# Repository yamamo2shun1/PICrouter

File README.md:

<div align="center">
<table>
<tr>
<th colspan="4" align="center">INDEX</th>
</tr>
<tr align="center">
    <td><a href="#how-to-buy">How to buy</a></td>
    <td><a href="#licenses">Licenses</a></td>
    <td><a href="#specifications">Specifications</a></td>
    <td><a href="#pin-assign">Pin Assign</a></td>
</tr>
<tr align="center">
    <td><a href="#development">Development</a></td>
    <td><a href="#bootloader-application">Bootloader App.</a></td>
    <td><a href="#schematic-and-board-current-ver-is-100">Sch & Brd Data</a></td>
    <td><a href="#application-projects">App. Projects</a></td>
</tr>
<tr align="center">
    <td><a href="#tutorial-jp">Tutorial (JP)</a></td>
    <td><a href="#tutorial-en">Tutorial (EN)</a></td>
    <td><a href="#supported-osc-messages">Supported OSC Msgs</a></td>
    <td><a href="#supported-hid-commands">Supported HID Cmds</a></td>
</tr>
</table>
</div>

PICrouter
======
PICrouter is a versatile and prototyping board specialized for [Open Sound Control].  
The main function is to communicate between OSC and USB-MIDI/HID.

PICrouter will be an useful with the following purpose.

* Develop an OSC/MIDI/HID controller for music or visual.
* Study a PIC32 microcontroller.
* Study a communication with usb and ethernet.
* Study a mruby(Support ONLY PIC32MX795F512H version)

Demo

* [Oto Devices Quick Demo][]
* [PICrouter and MobMuPlat OSC Demo][]
* [PICrouter and touchOSC Demo: PWM Control][]
* [LED Step Sequencer Test with PICrouter and LED_PAD_16][]
* [LED Intensity Control Test with PICrouter and LED_PAD_16][]
* [Multiple LED_ENC_ABS_32 Control Test from PICrouter][]
* [Intensity Control Test of RGB_PAD_16 from PICrouter][]
* [RGB Step Sequencer Test][]

[Open Sound Control]:http://opensoundcontrol.org

[Oto Devices Quick Demo]:https://vimeo.com/67548325
[PICrouter and MobMuPlat OSC Demo]:http://www.youtube.com/watch?v=xbNTXSsHR5w
[PICrouter and touchOSC Demo: PWM Control]:http://www.youtube.com/watch?v=srX1inH3xIY
[LED Step Sequencer Test with PICrouter and LED_PAD_16]: http://youtu.be/5rHGf42VQA8
[LED Intensity Control Test with PICrouter and LED_PAD_16]: http://youtu.be/yXPXuEcpFhE
[Multiple LED_ENC_ABS_32 Control Test from PICrouter]: http://youtu.be/imvcYX0qTLs
[Intensity Control Test of RGB_PAD_16 from PICrouter]: https://vimeo.com/70006217
[RGB Step Sequencer Test]: https://vimeo.com/73281314

<div align="center">

</div>
<div align="right">
Photographed by Kiyasu/TechnikLAB*
</div>

How to buy
------
You can buy the PICrouter on <a href="http://atelier.tkrworks.net/shop/index.php?main_page=product_info&cPath=2&products_id=29&language=en">tkrworks online store</a> and <a href="http://www.switch-science.com/catalog/1338/">SWITCH SCIENCE</a>.  
The price of product is 7560JPY.

Licenses
------
PICrouter is **Free Hardware** and **Free Software**.
* Hardware : [Creative Commons Attribute-ShareAlike 3.0 Unported][cc-by-sa]  
* Software : GNU General Public License version 3  

[cc-by-sa]:http://creativecommons.org/licenses/by-sa/3.0/ "Creative Commons Attribute-ShareAlike 3.0 Unported"

Specifications
------
0. Supported mruby(ONLY PIC32MX795F512H version)
1. Supported mDNS(Bonjour on Mac OS X), DHCP(both server and client).
2. Supported Open Sound Control.
3. Supported the multicast address(224.0.0.1 and 224.0.0.251).
4. Supported USB dual role function(DEVICE:MIDI & HID composite / HOST:MIDI & CDC composite).
5. Supported [USB HID bootloader][an1388] on Mac OS X and Windows.
6. PIC32MX675F512H(Freq:80MHz / FLASH:512K / RAM:64K) or PIC32MX795F512H(Freq:80MHz / FLASH:512K / RAM:128K)
7. A/D port x14
8. PWM output x4
9. SPI x2, I2C x3, UART x1, JTAG x1 and CAN x1
10. 100mm x 33.5mm, 4-layers board

[an1388]:http://www.microchip.com/stellent/idcplg?IdcService=SS_GET_PAGE&nodeId=1824&appnote=en554836

Pin Assign
------
<div align="center">

</div>

Development
------
* Microchip [MPLABX] v2.00
* Microchip [MPLAB XC32 Compiler] v1.22  
  *To develop application, you can use free version.*

[MPLABX]: http://www.microchip.com/pagehandler/en-us/family/mplabx/
[MPLAB XC32 Compiler]: http://www.microchip.com/pagehandler/en_us/devtools/mplabxc/

Bootloader Application
------
* PIC32UBL.exe (Win / Download is [here][an1388])
* PIC32UBL.maxpat (Mac / See the readme.txt in the folder "PICrouter/PIC32UBL_Max")

Schematic and Board (current ver. is 1.00)
--------------------------------
PICrouter.sch and .brd are drawn by Eagel v6.  
Additionaly, we use [Sparkfun eagle library][sparkfun].  
This library is also licensed by CC by-SA 3.0.  

And then We extend a special thank you to Tomoya(@tomoya723) and Rundog(@rundog).  
Tomoya gave many advices for designing of this board.  
Rundog assisted us with this board's production.

[sparkfun]: http://www.opencircuits.com/SFE_Footprint_Library_Eagle

Application Projects
------
#### PICrouter_HIDBL (current ver. is v1.1)  
  PICrouter_HIDBL.X is the USB HID Bootloader project files.  
  Look at [AN1388][] for details.  

[AN1388]: http://www.microchip.com/stellent/idcplg?IdcService=SS_GET_PAGE&nodeId=1824&appnote=en554836 "AN1388"

#### PICrouter (current ver. is 1.13.0) Updated 2014/04/24  
  PICrouter is for Open Sound Control and USB Dual Role.  
  PICrouter.X is this project folder.  
  The Max6 demo patches are in Max_Demo_Patchexs folder.  

#### PICrouter for mruby (current ver. is 0.2.3) Updated 2014/02/22  
  PICrouter for mruby supports mruby, Open Sound Control and USB Dual Role.  
  PICrouter_795_mrb.X is this project folder.
  
Tutorial (JP)
--------------------------------
Tutorial 0 : [まずはじめに][]  
Tutorial 1 : [OSCを使ったデジタル入出力の制御][]  
Tutorial 2 : [OSCを使ったアナログ入力の制御][]  
Tutorial 3 : [OSCを使ったPWMの制御][]  
Tutorial 4 : [OSCを使ったSPIの制御][]  
Tutorial 5 : [システム設定の変更][]  
Tutorial 6 : [MIDIをOSCに変換する][]  
Tutorial 7 : [ファームウェアの書き換え][]  
Tutorial 8 : [LED_ENC_32をPICrouterからOSCで制御][]  
Tutorial 9 : [LED_ENC_ABS_32をPICrouterからOSCで制御][]  
Tutorial 10 : [LED_PAD_16をPICrouterからOSCで制御][]

[まずはじめに]: https://github.com/tkrworks/PICrouter/wiki/まずはじめに
[OSCを使ったデジタル入出力の制御]: https://github.com/tkrworks/PICrouter/wiki/OSCを使ったデジタル入出力の制御
[OSCを使ったアナログ入力の制御]: https://github.com/tkrworks/PICrouter/wiki/OSCを使ったアナログ入力の制御
[OSCを使ったPWMの制御]: https://github.com/tkrworks/PICrouter/wiki/OSCを使ったPWM出力の制御
[OSCを使ったSPIの制御]: https://github.com/tkrworks/PICrouter/wiki/OSCを使ったSPIの制御
[システム設定の変更]: https://github.com/tkrworks/PICrouter/wiki/システム設定の変更
[MIDIをOSCに変換する]: https://github.com/tkrworks/PICrouter/wiki/MIDIをOSCに変換する
[ファームウェアの書き換え]: https://github.com/tkrworks/PICrouter/wiki/ファームウェアの書き換え
[LED_ENC_32をPICrouterからOSCで制御]: https://github.com/tkrworks/PICrouter/wiki/LED_ENC_32をPICrouterで制御
[LED_ENC_ABS_32をPICrouterからOSCで制御]: https://github.com/tkrworks/PICrouter/wiki/LED_ENC_ABS_32をPICrouterで制御
[LED_PAD_16をPICrouterからOSCで制御]: https://github.com/tkrworks/PICrouter/wiki/LED_PAD_16をPICrouterで制御

Tutorial (EN)
--------------------------------
Tutorial 0 : [Introduction][]  
Tutorial 1 : [Digital IO Control with OSC][]  
Tutorial 2 : [Analog Input Control with OSC][]  
Tutorial 3 : [PWM Output Control with OSC][]  
Tutorial 4 : [SPI Configuration with OSC][]  
Tutorial 5 : [System Configuration with OSC][]  
Tutorial 6 : [OSC-MIDI Bridge][]  
Tutorial 7 : [Firmware Update][]  
Tutorial 8 : [Control LED_ENC_32 from PICrouter with OSC][]  
Tutorial 9 : [Control LED_ENC_ABS_32 from PICrouter with OSC][]  
Tutorial 10 : [Control LED_PAD_16 from PICrouter with OSC][]

[Introduction]: https://github.com/tkrworks/PICrouter/wiki/Introduction
[Digital IO Control with OSC]: https://github.com/tkrworks/PICrouter/wiki/Digital-IO-Control-with-OSC
[Analog Input Control with OSC]: https://github.com/tkrworks/PICrouter/wiki/Analog-Input-Control-with-OSC
[PWM Output Control with OSC]: https://github.com/tkrworks/PICrouter/wiki/PWM-Output-Control-with-OSC
[SPI Configuration with OSC]: https://github.com/tkrworks/PICrouter/wiki/SPI-Configuration-with-OSC
[System Configuration with OSC]: https://github.com/tkrworks/PICrouter/wiki/System-Configuration-with-OSC
[OSC-MIDI Bridge]: https://github.com/tkrworks/PICrouter/wiki/OSC-MIDI-Bridge
[Firmware Update]: https://github.com/tkrworks/PICrouter/wiki/Firmware-Update
[Control LED_ENC_32 from PICrouter with OSC]: https://github.com/tkrworks/PICrouter/wiki/Control-LED_ENC_32-from-PICrouter
[Control LED_ENC_ABS_32 from PICrouter with OSC]: https://github.com/tkrworks/PICrouter/wiki/Control-LED_ENC_ABS_32-from-PICrouter
[Control LED_PAD_16 from PICrouter with OSC]: https://github.com/tkrworks/PICrouter/wiki/Control-LED_PAD_16-from-PICrouter-with-OSC

Supported OSC Messages
--------------------------------
See [osc pages][].

[osc pages]: https://github.com/tkrworks/PICrouter/wiki/Supported-OSC-Messages

Supported HID Commands
--------------------------------
See [hid pages][].

[hid pages]: https://github.com/tkrworks/PICrouter/wiki/Supported-HID-Commands

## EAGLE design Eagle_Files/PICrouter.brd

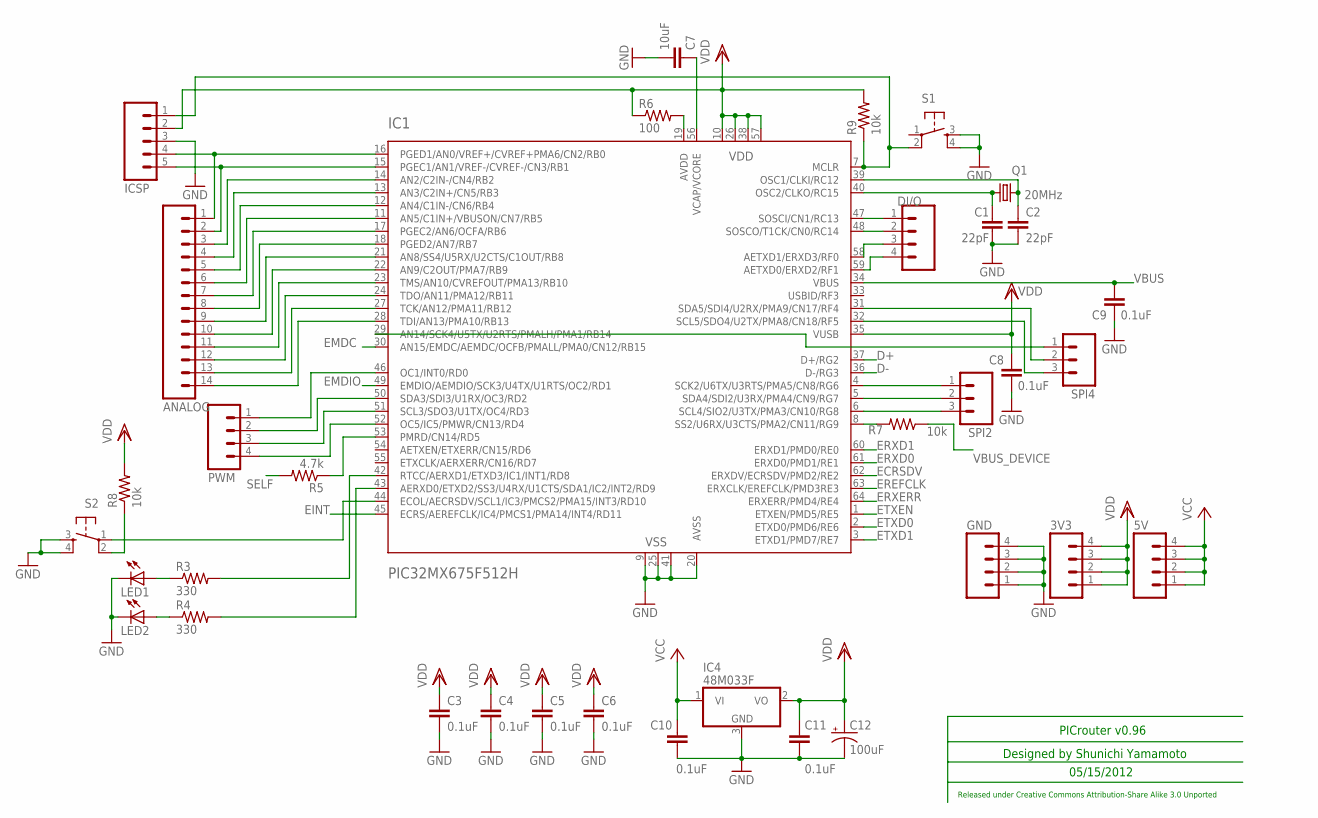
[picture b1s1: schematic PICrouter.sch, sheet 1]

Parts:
3V3, 5V: M04PTH; 1X04
ANALOG: M14; 1X14
C1, C2: 22pF; C2012
C3, C4, C5, C6, C8, C9, C10, C11: 0.1uF; C2012
C7: 10uF; C2012
C12: 100uF; PANASONIC_C
DI/O: M04PTH; 1X04
GND: M04PTH; 1X04
IC1: PIC32MX675F512H; TQFP64-10X10
IC4: 48M033F; TO252
ICSP: M05PTH; 1X05
LED1, LED2: LEDCHIP-LED0603; CHIP-LED0603
PWM: M04PTH; 1X04
Q1: 20MHz; CTS406
R3, R4: 330; 0603-RES
R5: 4.7k; 0603-RES
R6: 100; 0603-RES
R7, R8, R9: 10k; 0603-RES
S1, S2: TAC_SWITCHSMD; TACTILE_SWITCH_SMD
SPI2, SPI4: M03PTH; 1X03

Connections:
D+: IC1.37 (D+/RG2); also elsewhere on the board
D-: IC1.36 (D-/RG3); also elsewhere on the board
ECRSDV: IC1.62 (ERXDV/ECRSDV/PMD2/RE2); also elsewhere on the board
EINT: IC1.45 (ECRS/AEREFCLK/IC4/PMCS1/PMA14/INT4/RD11); also elsewhere on the board
EMDC: IC1.30 (AN15/EMDC/AEMDC/OCFB/PMALL/PMA0/CN12/RB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); also elsewhere on the board
EMDIO: IC1.49 (EMDIO/AEMDIO/SCK3/U4TX/U1RTS/OC2/RD1); also elsewhere on the board
EREFCLK: IC1.63 (ERXCLK/EREFCLK/PMD3RE3); also elsewhere on the board
ERXD0: IC1.61 (ERXD0/PMD1/RE1); also elsewhere on the board
ERXD1: IC1.60 (ERXD1/PMD0/RE0); also elsewhere on the board
ERXERR: IC1.64 (ERXERR/PMD4/RE4); also elsewhere on the board
ETXD0: IC1.2 (ETXD0/PMD6/RE6); also elsewhere on the board
ETXD1: IC1.3 (ETXD1/PMD7/RE7); also elsewhere on the board
ETXEN: IC1.1 (ETXEN/PMD5/RE5); also elsewhere on the board
GND: C1.2, C2.2, C3.2, C4.2, C5.2, C6.2, C7.2, C8.2, C9.1, C10.2, C11.2, C12.-, GND.1, GND.2, GND.3, GND.4, IC1.9 (GND), IC1.20 (AVSS), IC1.25 (GND), IC1.41 (GND), IC4.3 (GND), ICSP.3, LED1.C, LED2.C, S1.3, S1.4, S2.3, S2.4; also elsewhere on the board
unnamed: C2.1, IC1.39 (OSC1/CLKI/RC12), Q1.3 (2)
unnamed: C1.1, IC1.40 (OSC2/CLKO/RC15), Q1.1
unnamed: ANALOG.2, IC1.15 (PGEC1/AN1/VREF-/CVREF-/CN3/RB1), ICSP.5
unnamed: ANALOG.1, IC1.16 (PGED1/AN0/VREF+/CVREF+PMA6/CN2/RB0), ICSP.4
unnamed: IC1.7 (MCLR), ICSP.1, R9.1, S1.2
unnamed: C7.1, IC1.56 (VCAP/VCORE)
unnamed: R8.1, S2.2
unnamed: IC1.19 (AVDD), R6.2
unnamed: IC1.53 (PMRD/CN14/RD5), R5.1
unnamed: IC1.8 (SS2/U6RX/U3CTS/PMA2/CN11/RG9), R7.2
unnamed: IC1.42 (RTCC/AERXD1/ETXD3/IC1/INT1/RD8), R3.2
unnamed: IC1.43 (AERXD0/ETXD2/SS3/U4RX/U1CTS/SDA1/IC2/IN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), R4.2
unnamed: LED1.A, R3.1
unnamed: LED2.A, R4.1
unnamed: IC1.44 (ECOL/AECRSDV/SCL1/IC3/PMCS2/PMA15/INT3/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), S2.1
unnamed: ANALOG.3, IC1.14 (AN2/C2IN-/CN4/RB2)
unnamed: ANALOG.4, IC1.13 (AN3/C2IN+/CN5/RB3)
unnamed: ANALOG.5, IC1.12 (AN4/C1IN-/CN6/RB4)
unnamed: ANALOG.6, IC1.11 (AN5/C1IN+/VBUSON/CN7/RB5)
unnamed: ANALOG.7, IC1.17 (PGEC2/AN6/OCFA/RB6)
unnamed: ANALOG.8, IC1.18 (PGED2/AN7/RB7)
unnamed: ANALOG.9, IC1.21 (AN8/SS4/U5RX/U2CTS/C1OUT/RB8)
unnamed: ANALOG.10, IC1.22 (AN9/C2OUT/PMA7/RB9)
unnamed: ANALOG.11, IC1.23 (TMS/AN10/CVREFOUT/PMA13/RB10)
unnamed: ANALOG.12, IC1.24 (TDO/AN11/PMA12/RB11)
unnamed: ANALOG.13, IC1.27 (TCK/AN12/PMA11/RB12)
unnamed: ANALOG.14, IC1.28 (TDI/AN13/PMA10/RB13)
unnamed: IC1.4 (SCK2/U6TX/U3RTS/PMA5/CN8/RG6), SPI2.1
unnamed: IC1.5 (SDA4/SDI2/U3RX/PMA4/CN9/RG7), SPI2.2
unnamed: IC1.6 (SCL4/SIO2/U3TX/PMA3/CN10/RG8), SPI2.3
unnamed: IC1.31 (SDA5/SDI4/U2RX/PMA9/CN17/RF4), SPI4.2
unnamed: IC1.32 (SCL5/SDO4/U2TX/PMA8/CN18/RF5), SPI4.3
unnamed: IC1.29 (AN14/SCK4/U5TX/U2RTS/PMALH/PMA1/RB14), SPI4.1
unnamed: IC1.46 (OC1/INT0/RD0), PWM.1
unnamed: DI/O.1, IC1.47 (SOSCI/CN1/RC13)
unnamed: IC1.50 (SDA3/SDI3/U1RX/OC3/RD2), PWM.2
unnamed: IC1.51 (SCL3/SDO3/U1TX/OC4/RD3), PWM.3
unnamed: IC1.52 (OC5/IC5/PMWR/CN13/RD4), PWM.4
unnamed: DI/O.2, IC1.48 (SOSCO/T1CK/CN0/RC14)
unnamed: DI/O.3, IC1.58 (AETXD1/ERXD3/RF0)
unnamed: DI/O.4, IC1.59 (AETXD0/ERXD2/RF1)
SELF: R5.2; also elsewhere on the board
VBUS: C9.2, IC1.34 (VBUS); also elsewhere on the board
VBUS_DEVICE: R7.1; also elsewhere on the board
VCC: 5V.1, 5V.2, 5V.3, 5V.4, C10.1, IC4.1 (VI); also elsewhere on the board
VDD: 3V3.1, 3V3.2, 3V3.3, 3V3.4, C3.1, C4.1, C5.1, C6.1, C8.1, C11.1, C12.+, IC1.10 (VDD), IC1.26 (VDD), IC1.35 (VUSB), IC1.38 (VDD), IC1.57 (VDD), IC4.2 (VO), ICSP.2, R6.1, R8.2, R9.2; also elsewhere on the board

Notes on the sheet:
PICrouter v0.96
Designed by Shunichi Yamamoto
05/15/2012
Released under Creative Commons Attribution-Share Alike 3.0 Unported

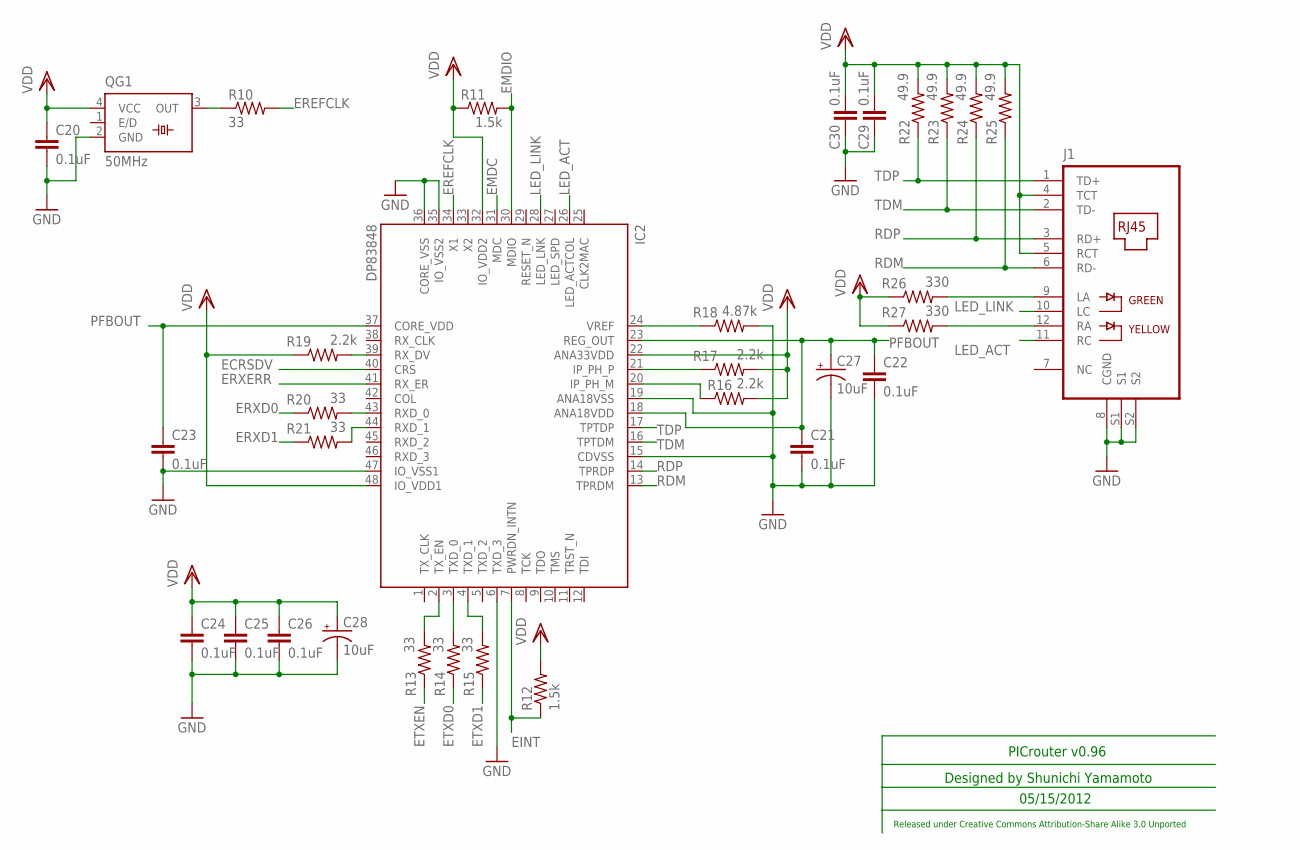
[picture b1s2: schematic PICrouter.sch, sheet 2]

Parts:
C20, C21, C22, C23, C24, C25, C26, C29, C30: 0.1uF; C2012
C27: 10uF; EIA6032
C28: 10uF; PANASONIC_C
IC2: DP83848; LQFP48
J1: J0011; PJ-J0
QG1: 50MHz; SM77H
R10, R13, R14, R15, R20, R21: 33; 0603-RES
R11, R12: 1.5k; 0603-RES
R16, R17, R19: 2.2k; 0603-RES
R18: 4.87k; 0603-RES
R22, R23, R24, R25: 49.9; 0603-RES
R26, R27: 330; 0603-RES

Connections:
ECRSDV: IC2.40 (CRS); also elsewhere on the board
EINT: IC2.7 (PWRDN_INTN), R12.1; also elsewhere on the board
EMDC: IC2.31 (MDC); also elsewhere on the board
EMDIO: IC2.30 (MDIO), R11.2; also elsewhere on the board
EREFCLK: IC2.34 (X1), R10.2; also elsewhere on the board
ERXD0: R20.1; also elsewhere on the board
ERXD1: R21.1; also elsewhere on the board
ERXERR: IC2.41 (RX_ER); also elsewhere on the board
ETXD0: R14.1; also elsewhere on the board
ETXD1: R15.1; also elsewhere on the board
ETXEN: R13.1; also elsewhere on the board
GND: C20.2, C21.2, C22.2, C23.2, C24.2, C25.2, C26.2, C27.P$2 (-), C28.-, C29.2, C30.2, IC2.6 (TXD_3), IC2.15 (CDVSS), IC2.19 (ANA18VSS), IC2.35 (IO_VSS2), IC2.36 (CORE_VSS), IC2.47 (IO_VSS1), J1.8 (CGND), J1.S1, J1.S2, QG1.2 (GND), R18.2; also elsewhere on the board
LED_ACT: IC2.26 (LED_ACTCOL), J1.11 (RC)
LED_LINK: IC2.28 (LED_LNK), J1.10 (LC)
unnamed: IC2.24 (VREF), R18.1
unnamed: IC2.21 (IP_PH_P), R17.1
unnamed: IC2.20 (IP_PH_M), R16.1
unnamed: IC2.39 (RX_DV), R19.2
unnamed: IC2.4 (TXD_1), R15.2
unnamed: IC2.3 (TXD_0), R14.2
unnamed: IC2.2 (TX_EN), R13.2
unnamed: J1.9 (LA), R26.2
unnamed: IC2.43 (RXD_0), R20.2
unnamed: IC2.44 (RXD_1), R21.2
unnamed: QG1.3 (OUT), R10.1
unnamed: J1.12 (RA), R27.2
PFBOUT: C21.1, C22.1, C23.1, C27.P$1 (+), IC2.18 (ANA18VDD), IC2.23 (REG_OUT), IC2.37 (CORE_VDD)
RDM: IC2.13 (TPRDM), J1.6 (RD-), R25.1
RDP: IC2.14 (TPRDP), J1.3 (RD+), R24.1
TDM: IC2.16 (TPTDM), J1.2 (TD-), R23.1
TDP: IC2.17 (TPTDP), J1.1 (TD+), R22.1
VDD: C20.1, C24.1, C25.1, C26.1, C28.+, C29.1, C30.1, IC2.22 (ANA33VDD), IC2.32 (IO_VDD2), IC2.48 (IO_VDD1), J1.4 (TCT), J1.5 (RCT), QG1.4 (VCC), R11.1, R12.2, R16.2, R17.2, R19.1, R22.2, R23.2, R24.2, R25.2, R26.1, R27.1; also elsewhere on the board

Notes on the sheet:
PICrouter v0.96
Designed by Shunichi Yamamoto
05/15/2012
Released under Creative Commons Attribution-Share Alike 3.0 Unported

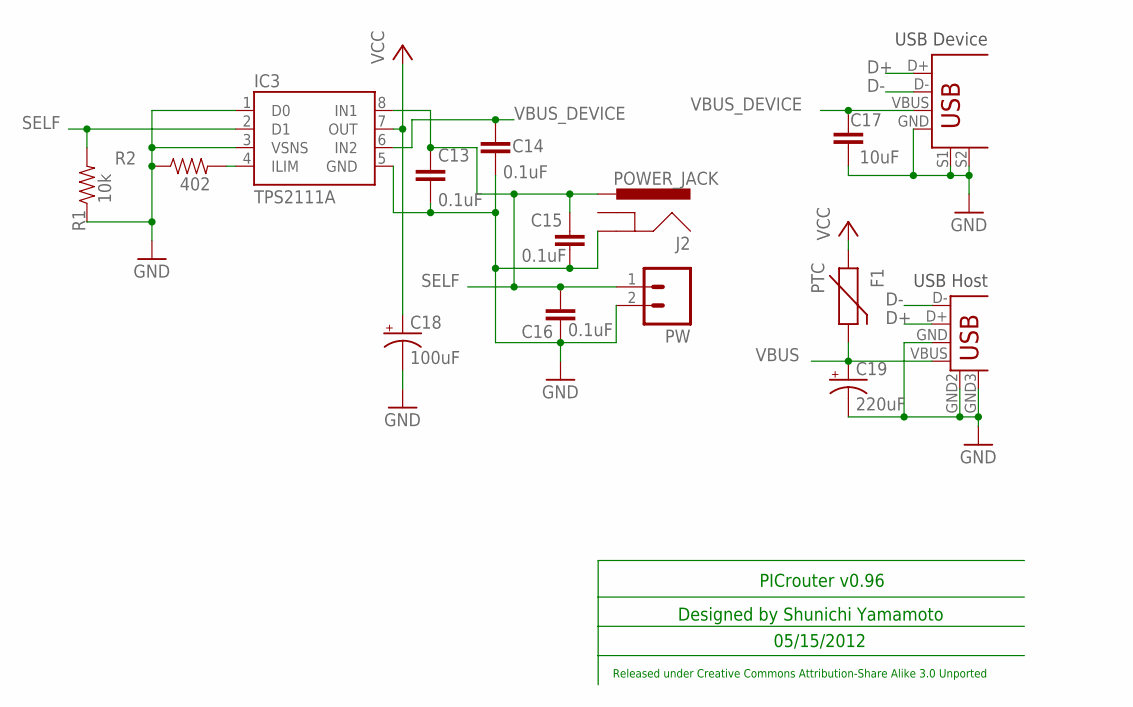
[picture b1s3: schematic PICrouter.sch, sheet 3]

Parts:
C13, C14, C15, C16: 0.1uF; C2012
C17: 10uF; C2012
C18: 100uF; PANASONIC_C
C19: 220uF; PANASONIC_D
F1: PTC; PTC-1206
IC3: TPS2111A; TSSOP8
J2: POWER_JACK; POWER_JACK_PTH_LOCK
PW: M02PTH; 1X02
R1: 10k; 0603-RES
R2: 402; 0603-RES
U2: DEVICE; USB-B-PTH
X2: USB-A-H

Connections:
D+: U2.D+, X2.D+; also elsewhere on the board
D-: U2.D-, X2.D-; also elsewhere on the board
GND: C13.2, C14.2, C15.2, C16.2, C17.2, C18.-, C19.-, IC3.1 (D0), IC3.3 (VSNS), IC3.5 (GND), J2.GND, PW.2, R1.1, R2.1, U2.GND, U2.S1, U2.S2, X2.GND, X2.GND2 (S1), X2.GND3 (S2); also elsewhere on the board
unnamed: IC3.4 (ILIM), R2.2
SELF: C13.1, C15.1, C16.1, IC3.2 (D1), IC3.8 (IN1), J2.PWR, PW.1, R1.2; also elsewhere on the board
VBUS: C19.+, F1.2, X2.VBUS; also elsewhere on the board
VBUS_DEVICE: C14.1, C17.1, IC3.6 (IN2), U2.VBUS; also elsewhere on the board
VCC: C18.+, F1.1, IC3.7 (OUT); also elsewhere on the board

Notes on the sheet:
USB Device
USB Host
PICrouter v0.96
Designed by Shunichi Yamamoto
05/15/2012
Released under Creative Commons Attribution-Share Alike 3.0 Unported

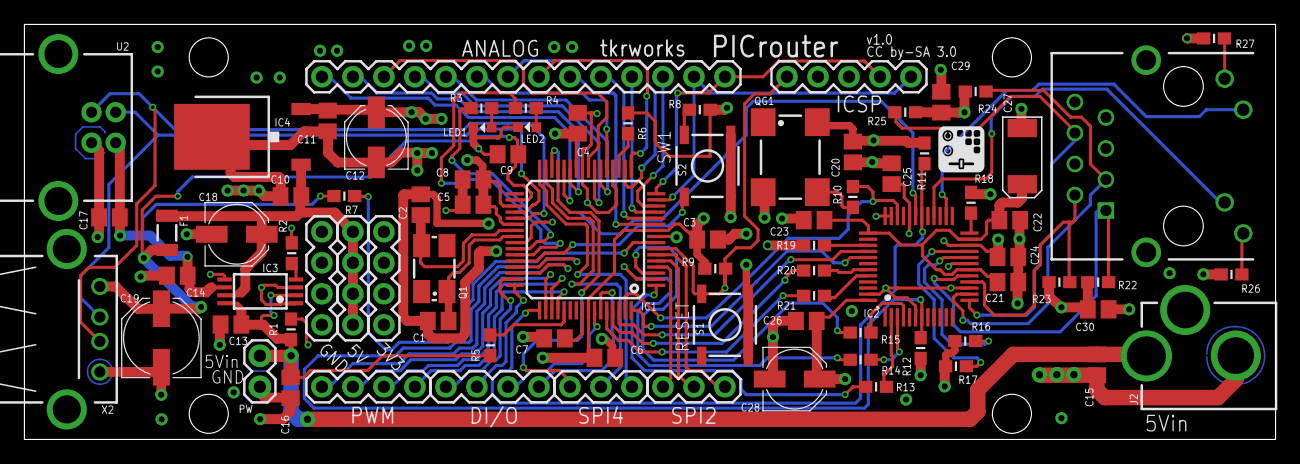
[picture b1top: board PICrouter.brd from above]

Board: 4 copper layers, 102.5 x 34.0 mm, 83 parts (0 on the bottom side), 80 nets.

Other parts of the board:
U$1: LOGO

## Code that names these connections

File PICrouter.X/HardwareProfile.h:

/*
 * Copylight (C) 2012, Shunichi Yamamoto, tkrworks.net
 *
 * This file is part of PICrouter.
 *
 * PICrouter is free software: you can redistribute it and/or modify
 * it under the terms of the GNU General Public License as published by
 * the Free Software Foundation, either version 3 of the License, or
 * (at your option ) any later version.
 *
 * PICrouter is distributed in the hope that it will be useful,
 * but WITHIOUT ANY WARRANTY; without even the implied warranty of
 * MERCHANTABILITY or FITNESS FOR A PARTICULAR PURPOSE.   See the
 * GNU General Public License for more details.
 *
 * You should have received a copy of the GNU General Public License
 * along with PICrouter. if not, see <http:/www.gnu.org/licenses/>.
 *
 * HardwareProfile.h,v.0.7 2013/03/26
 */

#ifndef HARDWARE_PROFILE_H
#define HARDWARE_PROFILE_H

/*******************************************************************/
/******** USB stack hardware selection options *********************/
/*******************************************************************/
//This section is the set of definitions required by the MCHPFSUSB
//  framework.  These definitions tell the firmware what mode it is
//  running in, and where it can find the results to some information
//  that the stack needs.
//These definitions are required by every application developed with
//  this revision of the MCHPFSUSB framework.  Please review each
//  option carefully and determine which options are desired/required
//  for your application.

#define USE_SELF_POWER_SENSE_IO
#define tris_self_power     TRISDbits.TRISD5    // Input
#define self_power          1

#define USE_USB_BUS_SENSE_IO
#define tris_usb_bus_sense  TRISGbits.TRISG9    // Input
#define USB_BUS_SENSE       1


// Clock frequency values
// These directly influence timed events using the Tick module.  They also are used for UART and SPI baud rate generation.
#define GetSystemClock()		(80000000ul)			// Hz
#define GetInstructionClock()	(GetSystemClock()/1)	// Normally GetSystemClock()/4 for PIC18, GetSystemClock()/2 for PIC24/dsPIC, and GetSystemClock()/1 for PIC32.  Might need changing if using Doze modes.
#define GetPeripheralClock()	(GetSystemClock()/1)	// Normally GetSystemClock()/4 for PIC18, GetSystemClock()/2 for PIC24/dsPIC, and GetSystemClock()/1 for PIC32.  Divisor may be different if using a PIC32 since it's configurable.

// using the PIC32 internal MAC interface
//#define TCPIP_IF_PIC32INT

// External National PHY configuration
#define	PHY_RMII				// external PHY runs in RMII mode
//#define	PHY_CONFIG_ALTERNATE	// alternate configuration used
#define	PHY_ADDRESS			0x1	// the address of the National DP83848 PHY

//State
#define HIGH 1
#define LOW  0

#define IO_OUT 0
#define IO_IN  1

//On Board Switch
#define initSW() TRISDbits.TRISD10 = 1;
#define SW_State() PORTDbits.RD10

//On Board LED Settings
#define initLEDs()     TRISDbits.TRISD8 = 0;\
                       TRISDbits.TRISD9 = 0;\
      	               LATDbits.LATD8 = 0;  \
                       LATDbits.LATD9 = 0;
#define LED_1          LATDbits.LATD8
#define LED_2          LATDbits.LATD9
#define LED_1_On()     LED_1 = 1;
#define LED_2_On()     LED_2 = 1;
#define LED_1_Off()    LED_1 = 0;
#define LED_2_Off()    LED_2 = 0;
#define LED_1_Toggle() LED_1 = !LED_1;
#define LED_2_Toggle() LED_2 = !LED_2;

//AD Pins Settings
#define ADC_AN0_IO(state)   TRISBbits.TRISB0  = state;
#define ADC_AN1_IO(state)   TRISBbits.TRISB1  = state;
#define ADC_AN2_IO(state)   TRISBbits.TRISB2  = state;
#define ADC_AN3_IO(state)   TRISBbits.TRISB3  = state;
#define ADC_AN4_IO(state)   TRISBbits.TRISB4  = state;
#define ADC_AN5_IO(state)   TRISBbits.TRISB5  = state;
#define ADC_AN6_IO(state)   TRISBbits.TRISB6  = state;
#define ADC_AN7_IO(state)   TRISBbits.TRISB7  = state;
#define ADC_AN8_IO(state)   TRISBbits.TRISB8  = state;
#define ADC_AN9_IO(state)   TRISBbits.TRISB9  = state;
#define ADC_AN10_IO(state)  TRISBbits.TRISB10 = state;
#define ADC_AN11_IO(state)  TRISBbits.TRISB11 = state;
#define ADC_AN12_IO(state)  TRISBbits.TRISB12 = state;
#define ADC_AN13_IO(state)  TRISBbits.TRISB13 = state;

#define ADC_AN0_OUT(state)  LATBbits.LATB0  = state;
#define ADC_AN1_OUT(state)  LATBbits.LATB1  = state;
#define ADC_AN2_OUT(state)  LATBbits.LATB2  = state;
#define ADC_AN3_OUT(state)  LATBbits.LATB3  = state;
#define ADC_AN4_OUT(state)  LATBbits.LATB4  = state;
#define ADC_AN5_OUT(state)  LATBbits.LATB5  = state;
#define ADC_AN6_OUT(state)  LATBbits.LATB6  = state;
#define ADC_AN7_OUT(state)  LATBbits.LATB7  = state;
#define ADC_AN8_OUT(state)  LATBbits.LATB8  = state;
#define ADC_AN9_OUT(state)  LATBbits.LATB9  = state;
#define ADC_AN10_OUT(state) LATBbits.LATB10 = state;
#define ADC_AN11_OUT(state) LATBbits.LATB11 = state;
#define ADC_AN12_OUT(state) LATBbits.LATB12 = state;
#define ADC_AN13_OUT(state) LATBbits.LATB13 = state;

#define ADC_AN0_IN()  PORTBbits.RB0
#define ADC_AN1_IN()  PORTBbits.RB1
#define ADC_AN2_IN()  PORTBbits.RB2
#define ADC_AN3_IN()  PORTBbits.RB3
#define ADC_AN4_IN()  PORTBbits.RB4
#define ADC_AN5_IN()  PORTBbits.RB5
#define ADC_AN6_IN()  PORTBbits.RB6
#define ADC_AN7_IN()  PORTBbits.RB7
#define ADC_AN8_IN()  PORTBbits.RB8
#define ADC_AN9_IN()  PORTBbits.RB9
#define ADC_AN10_IN() PORTBbits.RB10
#define ADC_AN11_IN() PORTBbits.RB11
#define ADC_AN12_IN() PORTBbits.RB12
#define ADC_AN13_IN() PORTBbits.RB13

// PWM
#define PWM_OC1_IO(state) TRISDbits.TRISD0 = state;
#define PWM_OC3_IO(state) TRISDbits.TRISD2 = state;
#define PWM_OC4_IO(state) TRISDbits.TRISD3 = state;
#define PWM_OC5_IO(state) TRISDbits.TRISD4 = state;
    
#define PWM_OC1_OUT(state) LATDbits.LATD0 = state;
#define PWM_OC3_OUT(state) LATDbits.LATD2 = state;
#define PWM_OC4_OUT(state) LATDbits.LATD3 = state;
#define PWM_OC5_OUT(state) LATDbits.LATD4 = state;

#define PWM_OC1_IN() PORTDbits.RD0
#define PWM_OC3_IN() PORTDbits.RD2
#define PWM_OC4_IN() PORTDbits.RD3
#define PWM_OC5_IN() PORTDbits.RD4

// DIO
#define D_PORT0_IO(state) TRISCbits.TRISC13 = state;
#define D_PORT1_IO(state) TRISCbits.TRISC14 = state;
#define D_PORT2_IO(state) TRISFbits.TRISF0  = state;
#define D_PORT3_IO(state) TRISFbits.TRISF1  = state;

#define D_PORT0_OUT(state) LATCbits.LATC13 = state;
#define D_PORT1_OUT(state) LATCbits.LATC14 = state;
#define D_PORT2_OUT(state) LATFbits.LATF0  = state;
#define D_PORT3_OUT(state) LATFbits.LATF1  = state;

#define D_PORT0_IN() PORTCbits.RC13
#define D_PORT1_IN() PORTCbits.RC14
#define D_PORT2_IN() PORTFbits.RF0
#define D_PORT3_IN() PORTFbits.RF1

// SPI4
#define SPI_SCK4_IO(state) TRISBbits.TRISB14 = state;
#define SPI_SDI4_IO(state) TRISFbits.TRISF4  = state;
#define SPI_SDO4_IO(state) TRISFbits.TRISF5  = state;

#define SPI_SCK4_OUT(state) LATBbits.LATB14 = state;
#define SPI_SDI4_OUT(state) LATFbits.LATF4  = state;
#define SPI_SDO4_OUT(state) LATFbits.LATF5  = state;

#define SPI_SCK4_IN() PORTBbits.RB14
#define SPI_SDI4_IN() PORTFbits.RF4
#define SPI_SDO4_IN() PORTFbits.RF5

// SPI2
#define SPI_SCK2_IO(state) TRISGbits.TRISG6 = state;
#define SPI_SDI2_IO(state) TRISGbits.TRISG7 = state;
#define SPI_SDO2_IO(state) TRISGbits.TRISG8 = state;

#define SPI_SCK2_OUT(state) LATGbits.LATG6 = state;
#define SPI_SDI2_OUT(state) LATGbits.LATG7 = state;
#define SPI_SDO2_OUT(state) LATGbits.LATG8 = state;

#define SPI_SCK2_IN() PORTGbits.RG6
#define SPI_SDI2_IN() PORTGbits.RG7
#define SPI_SDO2_IN() PORTGbits.RG8

#endif  //HARDWARE_PROFILE_H

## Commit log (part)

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2013-03-30 Updated README.
2013-03-30 Create gh-pages branch via GitHub
2013-03-30 Improved the send/receive function for OSC.
2013-03-30 Renewed the version.
2013-03-30 Changed the oscPacket array size.
2013-03-30 Supported the DHCP server when the USB mode is host.
2013-03-30 Disabled the NBNS.
2013-03-30 Fixed the memory leak in getStringArgumentAtIndex().
2013-04-02 Improved the overall performance of the OSC send/receive processing.
2013-04-02 Fixed some indents.
2013-04-02 Fixed the calculation bug of the total data size in the OSC message included string.
2013-04-02 Modified the version number.
2013-04-02 Deleted my time delay functions.
2013-04-02 Added TimeDelay.h/.c of Microchip library.
2013-04-02 Changed the time delay functions.
2013-04-02 Changed the time delay function.
2013-04-02 Deleted an argument for debug.
2013-04-02 Improved the functions for comparing an address of OSC messages.
2013-04-03 Added some files for the USB HID Host in this project.
2013-04-03 Modified some definitions to support the USB HID Host.
2013-04-06 Commented out the debug functions.
2013-04-06 Commented out the unsupported definition.
2013-04-06 v0.9.30 release
    Supported the OSC bundle.
    Supported the control from the iOS/android app such as touchOSC.
2013-04-06 Enabled the NetBIOS and Zeroconf Link-Local.
2013-04-06 Disabled some definitions for USB HID.
2013-04-06 PICrouter firmware v1.4.10 release.
    Supported the OSC bundle.
    Supported the iOS/android app such as touchOSC.
    Supported the NetBIOS and Zeroconf Link-Local Addressing.
2013-04-06 Added the NBNS.h/.c and changed the heap size.
2013-04-07 Added some OSC messages for touchOSC.
2013-04-07 Support some OSC messages to control the PWM from touchOSC.
2013-04-12 Deleted some lines.
2013-04-12 Modified the condition to compare type tags of OSC.
2013-04-12 Supported the multicast address "224.0.0.1".
2013-04-17 v1.0 release
    Supported to send an OSC Bundle.
2013-04-17 Modified the network settings
    Increased the RX buffer size
    Enabled ICMP Client
    Disabled ICMP Server
    Disabled AUTO IP
    Disabled NetBIOS
    Disabled Zeroconf Link-Local
2013-04-17 PICrouter firmware v1.5.0 Release
    Supported to send an OSC bundle.
    Modified some network configurations.
    Improved the performance of the OSC communication.
2013-04-17 Commented out the RXSIZE's preprocessor condition.
2013-04-21 Fixed some bugs.
2013-04-21 Modified timer1's period from 0x0FFF to 0xFFFF.
2013-04-21 Modified the default IP settings and the buffer size.
2013-04-23 Modified the buffer size.
2013-04-23 Modified some codes.
2013-04-23 Changed how to access the global variables in the OSC library.
2013-04-23 encoder.h/.c v0.60 release
    Supported the LED_ENC_ABS_32 module.
    Changed the all global variables to static variables.
    Added the set/get functions to access static variables.
2013-04-23 pic router.h/.c v1.5.1 release
    Supported the LED_ENC_ABS_32 module.
    Added new OSC messages to control the LED_ENC_ABS_32.
    Changed how to access to the global variables in the library.
    Modified the sendOSCTask() function for the timer5 interrupt.
    Improved the OSC sending and receiving performance.
2013-04-24 Modified the interrupt level from 2 to 7.
2013-04-24 Fixed how to connect the LED_ENC_ABS_32.
2013-04-24 Fixed the ring buffer process.
2013-04-24 Added the script to refresh the mDNSResponder.
2013-04-24 Deleted a volatile modifier.
2013-04-24 Commented out the timer functions.
2013-04-25 Changed some BYTE variables to int.
2013-04-25 Deleted some volatile modifiers.
2013-04-26 Modified the address string of some OSC messages.
2013-04-26 Fixed some bugs receiving some OSC messages.
    /std/kit/rotary/led/bits/set
    /std/kit/rotary/led/step/set
    /std/kit/rotary/led/intensity/set
    /std/kit/rotary/led/intensity/get
    /std/kit/rotary/led/intensity/all/set
2013-05-01 encoder.h/.c v0.6.2 release
    Supported the LED_ENC_32.
2013-05-01 osc.h/.c v1.0.4 release
    Supported the LED_ENC_32.
    Modified some OSC message's address names.
2013-05-01 PICrouter firmware v1.5.3 release
    Supported the LED_ENC_32.
    Fixed some bugs.
2013-05-04 encoter.h/.c v0.6.3 release
    Deleted the timer interrupt function.
    (Moved to the pic router.c)
2013-05-04 Deleted the dwLedSequence array.
2013-05-04 Supported the LED_PAD_16 module.
2013-05-04 Added the OSC messages to control the LED_PAD_16.
2013-05-15 Fixed some bugs of the LEDs intensity control.
2013-05-20 Fixed a bug of an OSC message receiving.
2013-05-20 Changed the default IP address from 169.254.1.2 to 192.168.1.2.
2013-05-20 Fixed a bug of the mDNS's auto rename service.
2013-05-23 added SC_Demo_Code/
2013-05-25 Deleted unnecessary arrays.
2013-05-25 Added the lcd.h/.c for a character LCD module.
2013-05-25 Appended the OSC message for a character LCD module.
2013-05-25 PICrouter firmware v1.5.8 release
    Supported to control a character LCD module with the OSC.
    Fixed some bugs.
2013-05-25 Fixed a bug.
2013-05-27 added 1_Digital_Demo.sc
2013-05-27 added 3_PWM_Demo.sc
2013-05-27 added 5_System_Configurations
2013-05-27 Change address variables
2013-06-14 Added new OSC messages for I2C.
2013-06-14 PICrouter firmware v1.5.9 release
    Added new OSC messages for I2C.
    * The current version only supports the Microchip serial eeprom 24LC256.
2013-06-16 Added some functions for I2C communication.
2013-06-16 PICrouter firmware v1.5.10 release.
    Supported to control I2C with OSC.
    * The latest version is only supported a master send/receive.
2013-06-16 Fixed a bug to send data from the master I2C.
2013-06-18 Fixed the bug of the OSC message "/sys/host/name/set".
2013-06-18 Changed the timer5 interval.
2013-06-19 Improved the processing when the rotary encoder is stopped.
2013-06-20 Added source and header files for USB host CDC.
2013-06-20 Added the USB host configurations for the host CDC.
2013-06-20 Added some OSC messages for the USB host CDC.
2013-06-24 PICrouter firmware v1.6.0 release
    Supported the USB MIDI and CDC composite host function.
2013-06-24 Renewed.
2013-06-25 Deleted unnecessary project.
2013-07-10 Added function comments and changed how to access an array.
2013-07-10 Commented out a definition.
2013-07-10 osc.h/.c v1.2.0 release
    Supported the RGB_PAD_16.
    Supported the OSC messages to adjust an analog value resolution(8bit or 10bit).
    Added function's comments.
2013-07-10 Enabled the STACK_USE_NBNS and STACK_USE_ZEROCONF_LINK_LOCAL.
2013-07-10 PICrouter firmware v1.7.0 release.
    Supported the OSC messages to control the RGB_PAD_16.
    Supported the OSC messages to adjust an analog value's resolution(8bit or 10bit).
    Added function's comments.
    Fixed some bugs.
2013-07-19 Disabled NetBIOS Service.
2013-07-19 Added some code for NetBIOS.
2013-07-19 Modified some project files because My develop environment is changed from Mac OS X 10.8 to Windows 8 Pro 64bit.
2013-07-19 PICrouter v1.7.1 release. Disabled the NetBIOS service.
2013-08-28 Supported the RGB_PAD_8 and RGB_PAD_16.
2013-08-28 Added the OSC messsages to support the RGB_PAD_8 and RGB_PAD_16.
2013-08-28 Renewed some project files.
2013-08-28 Recompiled the binary files.
2013-08-28 Added the OSC messages to read and write the NVM(Flash area).
2013-08-28 PICrouter firmware v1.9.0 Release. Supported the NVM read/write functions from the OSC.
2013-08-29 Updated the mxj libraries.
2013-08-29 Modified the library path.
2013-08-29 Modified some parts in patch for Max 6.1.3.
2013-08-29 Added the readme.txt.
2013-08-29 Re-commited.
2013-09-05 Disabled the STACK_ZEROCONF_LINK_LOCAL.
2013-09-05 Improved the RGB_PAD_16/8's control performance.
2013-09-05 Added the OSC messages "/sys/discover/devices" and "/sys/discovered/device" to discover a PICrouter which connected to a local network.
2013-09-05 PICrouter firmware v1.10.0 Release. Supported a function to discover a PICrouter which connected to a local network. Improved the RGB_PAD_16/8's LED control performance. Disabled the Zeroconf Link Lo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
2013-09-06 Modified some compile options.
2013-09-06 Moved the include sentences from source to header.
2013-09-06 PICrouter firmware v1.10.1 Release. Improved the OSC message to discover a PICrouter. Fixed some bugs.
2013-11-18 Moved the Microchip USB and TCPIP libraries and tkrworks libraries from project folder to "tkrworks-libs" folder. Added sram.h/.c. Modified Include directories configuration.
2013-11-18 PICrouter firmware v1.11.0 release Supported to use an external SRAM(Microchip 23K256) with the OSC processing. Changed the timer of PWM from timer23 to timer2.
2013-11-18 Updated REAMDE
2013-11-22 Enabled the definition "USE_SPI_SRAM" by default.
2013-11-22 Enabled the stack of Zroconf Link-Local.
2013-11-22 Updated the Microchip Libraries for Applications.
2013-11-22 Added the makefiles for PIC32MX795F512H.
2013-11-22 Added .bash file for PIC32MX795F512H.
2013-11-22 Added the HEX and ELF files compiled for PIC32MX795F512H.
2013-11-22 Deleted unused files for this project and recompiled.
2013-11-22 Added some configurations to compile the PICrouter for mruby in the project properties.
2013-11-23 Deleted unnecessary file.
2013-11-23 Changed the UDP and OSC buffer size.
2013-11-23 Changed some configurations.
2014-02-15 the following functions are added.
    1. setOSCAddress
    2. setOSCTypeTag
    3. addOSCIntArgument
    4. addOSCFloatArgument
    5. addOSCStringArgument
    6. clearOSCMessage
2014-02-15 Modified the EMAC_RX_BUFF_SIZE from 256 to 512.
2014-02-15 Renewed some configuration files.
2014-02-15 Added some neccessary files to build mruby on PICrouter.
2014-02-17 Modified mruby library path from "mruby-master" to "mruby-1.0.0"
2014-02-17 PICrouter for mruby ver.0.2.1 release. Changed mruby version from github head to stable v1.0.0. fixed the bug of the host name initialization.
2014-02-18 Modified some configurations.
2014-02-22 Deleted picrouter.rb
2014-02-22 Modified the I2C's control way.
2014-02-22 Adjusted some line's indents and spaces.
2014-02-22 Added header and source files for the USB callback functions.
2014-02-22 Modified the following build configurations.
    1. Optimize Level
    2. Minimum Heap Size
    3. mruby Build Options(cc.defines)
2014-02-22 Renewed the timestamp.
2014-02-22 PICrouter v0.2.3 release.
    Moved the USB callback functions to the usb_callback.h/.c.
    Added some functions for mruby.
    Separated the OSC received process to the following parts.
    1. Standard Messages
    2. MIDI Messages
    3. CDC Messages
2014-02-22 PICrouter v0.2.3 release.
    Improved the OSC receive processing.
2014-02-24 PICrouter v1.12.0 release.
    Deleted the USB callback functions and global variables in picrouter.c.
    Added header and source file(usb_callback.h/.c) for the USB callback functions.
    Fixed the initialization of the host name.
2014-02-24 Added the usb_callback.h/.c in the project.
2014-02-24 Deleted some commented line.
2014-02-24 Renewed
2014-03-03 Modified the macro's name for turning on and off the onboard LEDs and getting onboard switch's state.
2014-03-03 Modified the I/O port control functions.
2014-03-03 Improved some functions for sending the MIDI note and control change messsage.
2014-03-03 Modified the include header file.
2014-04-15 Added the new function "sendPad4()" for the PItCh controller.
2014-04-15 Enclosed the USBHostCDCTransfer by the #if defined(USB_USE_CDC) and #endif
2014-04-15 Commented out the debug code.
2014-04-15 Enclosed some defenitions by the #if defined(USB_USE_MIDI) and #endif.
2014-04-15 PICrouter v1.12.2 is released. Fixed the bug of the host USB_MIDI sending and receiving process.
2014-04-15 Added codes to free the memory.
2014-04-25 Added some functions to send and receive the OSC messages via WiFly RN-131C module.
2014-04-25 PICrouter firmware v1.13.0 release. Supported the WiFly RN-131C module. Changed the priority of Time4 and Timer5.
2014-08-05 Supported the DAC+ADC Shield for PICrouter. Supported the UART Wi-Fi module RN134(131).
2014-08-05 Supported the RGB_PAD_8L.
2014-08-05 Changed the EMAC_RX_BUFF_SIZE.
2014-08-05 PICrouter firmware v1.15.0 is released.
    Supported the UART Wi-Fi module RN134(131).
    Supported the RGB_PAD_8L
    Supported the DAC+ADC Shield for PICrouter.
2014-08-05 PICrouter for mruby v0.2.5 is released.
